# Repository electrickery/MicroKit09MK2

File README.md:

## Description

In several 1983 editions of the French computer magazine 'Led' an MC6809 
single board computer was published, supporting a 6-digit, 7-segment Led 
display and 34 keys. The original has a 2 kByte monitor ROM and 2 kByte 
RAM. 

<p align="center">

Most published material can be found here: 
https://lab.nethence.com/frederic/Microit09/

This is a recreation, with a smaller footprint and some room for 
expansion.

The original, published monitor version is 1.8. This repository contains
my minor enhancements.

My webpage on the subject can be found here: 
http://electrickery.nl/comp/microKit09/

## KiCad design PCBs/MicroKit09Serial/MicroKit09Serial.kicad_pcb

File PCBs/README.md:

MicroKit09 and MicroKit09_OI are the CPU and I/O (display, keyboard & 
cassette interface) boards.

The main differences from the 1980's original are:
* the form factor, 
* inter-board connector, 
* display type,
* keyboard construction,
* expansion connector (most pins use the 6809 pinout),
* ROM-size jumper (2 kByte / 4 kByte),
* RAM size jumper (2 kByte / 8 kByte),
* controllable LED on CPU-board (connects to PIA-CB2, also cassette out),
* added more address decoding for the I/O segment at A000h, reducing the
  memory range of the PIA to 1 kByte (was 8 kByte). A chip-select signal
  for A400h-A7FFh is available on the expansion connector.

MicroKit09Serial is the (as yet) untested serial interface.

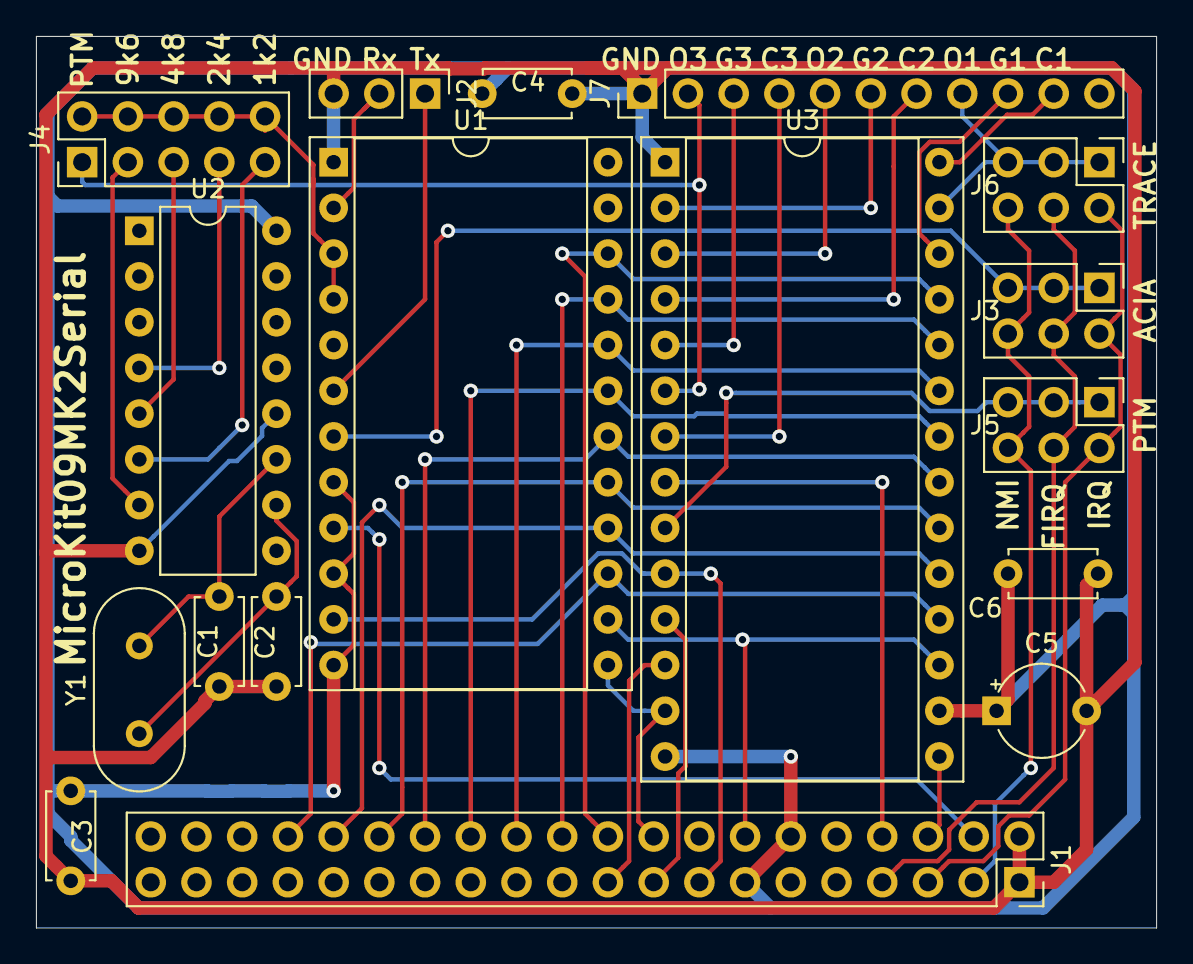
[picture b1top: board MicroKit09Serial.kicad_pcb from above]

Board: 2 copper layers, 62.2 x 49.5 mm, 17 parts (0 on the bottom side), 41 nets.

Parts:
C1, C2: 22pF; C_Disc_D4.7mm_W2.5mm_P5.00mm
C3, C4, C6: 100nF; C_Disc_D4.7mm_W2.5mm_P5.00mm
C5: 100uF/16V; CP_Radial_Tantal_D5.0mm_P5.00mm
J1: ExpansionConnector; PinHeader_2x20_P2.54mm_Vertical_CW
J2: Serial; PinHeader_1x03_P2.54mm_Vertical
J3: ACIA_INT; PinHeader_2x03_P2.54mm_Vertical
J4: BaudrateSelect; PinHeader_2x05_P2.54mm_Vertical
J5: PTM_INT; PinHeader_2x03_P2.54mm_Vertical
J6: TRACE_INT; PinHeader_2x03_P2.54mm_Vertical
J7: PTM; PinHeader_1x11_P2.54mm_Vertical
U1: MC6850; DIP-24_W15.24mm_Socket
U2: 4060N; DIP-16_W7.62mm
U3: MC6840; DIP-28_W15.24mm_Socket
Y1: 2.4576MHz; Crystal_HC49-U_Vertical

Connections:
+5V: C3.1, C4.1, C5.1, C6.1, J1.7, J1.35, U1.8, U1.10, U1.12, U2.16, U3.14, U3.16
/1200Bd: J4.9, U2.6
/2400Bd: J4.7, U2.4
/4800Bd: J4.5, U2.5
/9600Bd: J4.3, U2.7
/A0: J1.8, U1.11, U3.10
/A1: J1.9, U3.11
/A2: J1.10, U3.12
/A400-A7FF*: J1.39, U1.9
/A800-ABFF*: J1.38, U3.15
/ACIA_IRQ*: J3.1, J3.3, J3.5, U1.7
/BaudRate: J4.2, J4.4, J4.6, J4.8, J4.10, U1.3, U1.4
/D0: J1.31, U1.22, U3.25
/D1: J1.30, U1.21, U3.24
/D2: J1.29, U1.20, U3.23
/D3: J1.28, U1.19, U3.22
/D4: J1.27, U1.18, U3.21
/D5: J1.26, U1.17, U3.20
/D6: J1.25, U1.16, U3.19
/D7: J1.24, U1.15, U3.18
/E: J1.34, U1.14, U3.17
/FIRQ*: J1.4, J3.4, J5.4, J6.4
/IRQ*: J1.3, J3.2, J5.2, J6.2
/NMI*: J1.2, J3.6, J5.6, J6.6
/PTM_C1*: J7.10, U3.28
/PTM_C2*: J7.7, U3.4
/PTM_C3*: J7.4, U3.7
/PTM_G1*: J7.9, U3.26
/PTM_G2*: J7.6, U3.2
/PTM_G3*: J7.3, U3.5
/PTM_IRQ*: J5.1, J5.3, J5.5, U3.9
/PTM_O1: J6.1, J6.3, J6.5, J7.8, U3.27
/PTM_O2: J7.5, U3.3
/PTM_O3: J4.1, J7.2, U3.6
/RESET*: J1.37, U3.8
/RW*: J1.32, U1.13, U3.13
GND: C1.2, C2.2, C3.2, C4.2, C5.2, C6.2, J1.1, J1.40, J2.3, J7.1, U1.1, U2.8, U2.12, U3.1
unnamed: C1.1, U2.11, Y1.2
unnamed: C2.1, U2.10, Y1.1
unnamed: J2.1, U1.6
unnamed: J2.2, U1.2

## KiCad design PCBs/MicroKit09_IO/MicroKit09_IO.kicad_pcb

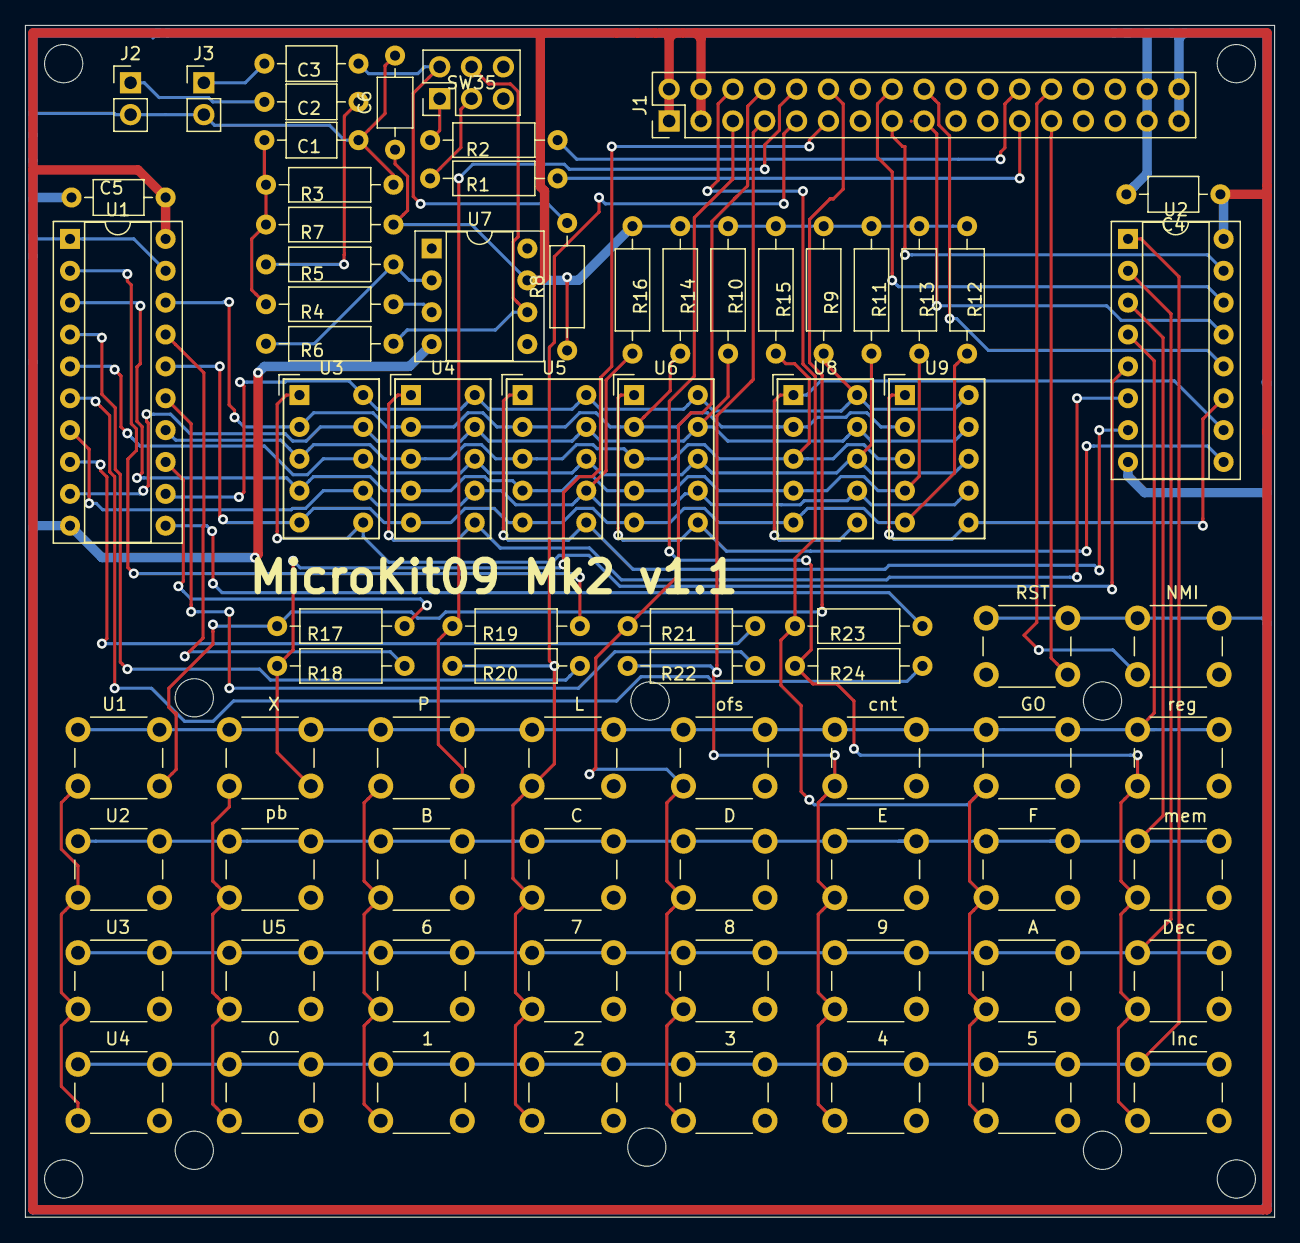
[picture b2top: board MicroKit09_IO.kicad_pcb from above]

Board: 2 copper layers, 99.6 x 95.0 mm, 77 parts (0 on the bottom side), 54 nets.

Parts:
C1, C2, C3, C4, C5: 100nF; C_Axial_L3.8mm_D2.6mm_P7.50mm_Horizontal
C6: 10uF; C_Axial_L3.8mm_D2.6mm_P7.50mm_Horizontal
J1: I/O-connector; PinHeader_2x17_P2.54mm_Vertical
J2: input; PinHeader_1x02_P2.54mm_Vertical
J3: output; PinHeader_1x02_P2.54mm_Vertical
R1, R2: 4k7; R_Axial_DIN0207_L6.3mm_D2.5mm_P10.16mm_Horizontal
R3: 27k; R_Axial_DIN0207_L6.3mm_D2.5mm_P10.16mm_Horizontal
R4, R5, R7: 10k; R_Axial_DIN0207_L6.3mm_D2.5mm_P10.16mm_Horizontal
R6: 1M; R_Axial_DIN0207_L6.3mm_D2.5mm_P10.16mm_Horizontal
R8: 470; R_Axial_DIN0207_L6.3mm_D2.5mm_P10.16mm_Horizontal
R9, R10, R11, R12, R13, R14, R15, R16: 120; R_Axial_DIN0207_L6.3mm_D2.5mm_P10.16mm_Horizontal
R17, R18, R19, R20, R21, R22, R23, R24: 5k6; R_Axial_DIN0207_L6.3mm_D2.5mm_P10.16mm_Horizontal
SW1: U1; SW_PUSH_6mm_H5mm
SW2: U2; SW_PUSH_6mm_H5mm
SW3: U3; SW_PUSH_6mm_H5mm
SW4: U4; SW_PUSH_6mm_H5mm
SW5: X; SW_PUSH_6mm_H5mm
SW6: pb; SW_PUSH_6mm_H5mm
SW7: U5; SW_PUSH_6mm_H5mm
SW8: 0; SW_PUSH_6mm_H5mm
SW9: P; SW_PUSH_6mm_H5mm
SW10: B; SW_PUSH_6mm_H5mm
SW11: 6; SW_PUSH_6mm_H5mm
SW12: 1; SW_PUSH_6mm_H5mm
SW13: L; SW_PUSH_6mm_H5mm
SW14: C; SW_PUSH_6mm_H5mm
SW15: 7; SW_PUSH_6mm_H5mm
SW16: 2; SW_PUSH_6mm_H5mm
SW17: ofs; SW_PUSH_6mm_H5mm
SW18: D; SW_PUSH_6mm_H5mm
SW19: 8; SW_PUSH_6mm_H5mm
SW20: 3; SW_PUSH_6mm_H5mm
SW21: cnt; SW_PUSH_6mm_H5mm
SW22: E; SW_PUSH_6mm_H5mm
SW23: 9; SW_PUSH_6mm_H5mm
SW24: 4; SW_PUSH_6mm_H5mm
SW25: GO; SW_PUSH_6mm_H5mm
SW26: F; SW_PUSH_6mm_H5mm
SW27: A; SW_PUSH_6mm_H5mm
SW28: 5; SW_PUSH_6mm_H5mm
SW29: reg; SW_PUSH_6mm_H5mm
SW30: mem; SW_PUSH_6mm_H5mm
SW31: Dec; SW_PUSH_6mm_H5mm
SW32: Inc; SW_PUSH_6mm_H5mm
SW33: NMI; SW_PUSH_6mm_H5mm
SW34: RST; SW_PUSH_6mm_H5mm
SW35: Cassette; PinHeader_2x03_P2.54mm_Vertical
U1: 74LS240; DIP-20_W7.62mm_Socket
U2: 74LS42; DIP-16_W7.62mm_Socket
U3, U4, U5, U6, U8, U9: HDSP-A153; HDSP-A151
U7: CA3140; DIP-8_W7.62mm_Socket

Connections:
+5V: C4.1, C5.1, C6.1, J1.1, J1.2, J1.3, J1.4, R3.2, R8.1, R9.2, R10.2, R11.2, R12.2, R13.2, R14.2, R15.2, R16.2, U1.20, U2.16, U7.7
/CB1: J1.23, R1.1
/CB2: J1.24, R2.1
/NMI*: J1.26, SW33.2
/PA0: J1.5, R24.2, SW29.2, SW30.2, SW31.2, SW32.2
/PA1: J1.6, R23.2, SW25.2, SW26.2, SW27.2, SW28.2
/PA2: J1.7, R22.2, SW21.2, SW22.2, SW23.2, SW24.2
/PA3: J1.8, R21.2, SW17.2, SW18.2, SW19.2, SW20.2
/PA4: J1.9, R20.2, SW13.2, SW14.2, SW15.2, SW16.2
/PA5: J1.10, R19.2, SW9.2, SW10.2, SW11.2, SW12.2
/PA6: J1.11, R18.2, SW5.2, SW6.2, SW7.2, SW8.2
/PA7: J1.12, R17.2, SW1.2, SW2.2, SW3.2, SW4.2
/PB0: J1.15, U2.15
/PB1: J1.16, U2.14
/PB2: J1.17, U2.13
/PB3: J1.18, U2.12
/R1: SW4.1, SW8.1, SW12.1, SW16.1, SW20.1, SW24.1, SW28.1, SW32.1, U2.1
/R2: SW3.1, SW7.1, SW11.1, SW15.1, SW19.1, SW23.1, SW27.1, SW31.1, U2.2
/R3: SW2.1, SW6.1, SW10.1, SW14.1, SW18.1, SW22.1, SW26.1, SW30.1, U2.3
/R4: SW1.1, SW5.1, SW9.1, SW13.1, SW17.1, SW21.1, SW25.1, SW29.1, U2.4
/RESET*: J1.25, SW34.2
GND: C1.2, C4.2, C5.2, C6.2, J1.31, J1.32, J1.33, J1.34, J2.2, J3.2, R7.1, SW33.1, SW34.1, U1.1, U1.10, U1.19, U2.8, U7.4
unnamed: C1.1, R3.1, R4.1, R7.2
unnamed: C2.1, J2.1
unnamed: C2.2, R5.1
unnamed: C3.1, J3.1
unnamed: C3.2, R8.2, SW35.2
unnamed: R1.2, SW35.3
unnamed: R2.2, SW35.1
unnamed: R4.2, U7.3
unnamed: R5.2, R6.1, U7.2
unnamed: R6.2, SW35.4, U7.6
unnamed: R9.1, U1.12, U3.10, U4.10, U5.10, U6.10, U8.10, U9.10
unnamed: R10.1, U1.9, U3.9, U4.9, U5.9, U6.9, U8.9, U9.9
unnamed: R11.1, U1.5, U3.8, U4.8, U5.8, U6.8, U8.8, U9.8
unnamed: R12.1, U1.16, U3.5, U4.5, U5.5, U6.5, U8.5, U9.5
unnamed: R13.1, U1.3, U3.4, U4.4, U5.4, U6.4, U8.4, U9.4
unnamed: R14.1, U1.18, U3.2, U4.2, U5.2, U6.2, U8.2, U9.2
unnamed: R15.1, U1.14, U3.3, U4.3, U5.3, U6.3, U8.3, U9.3
unnamed: R16.1, U1.7, U3.7, U4.7, U5.7, U6.7, U8.7, U9.7
unnamed: R17.1, U1.13
unnamed: R18.1, U1.17
unnamed: R19.1, U1.2
unnamed: R20.1, U1.4
unnamed: R21.1, U1.8
unnamed: R22.1, U1.15
unnamed: R23.1, U1.11
unnamed: R24.1, U1.6
unnamed: U2.5, U3.1, U3.6
unnamed: U2.6, U4.1, U4.6
unnamed: U2.7, U5.1, U5.6
unnamed: U2.9, U6.1, U6.6
unnamed: U2.10, U8.1, U8.6
unnamed: U2.11, U9.1, U9.6

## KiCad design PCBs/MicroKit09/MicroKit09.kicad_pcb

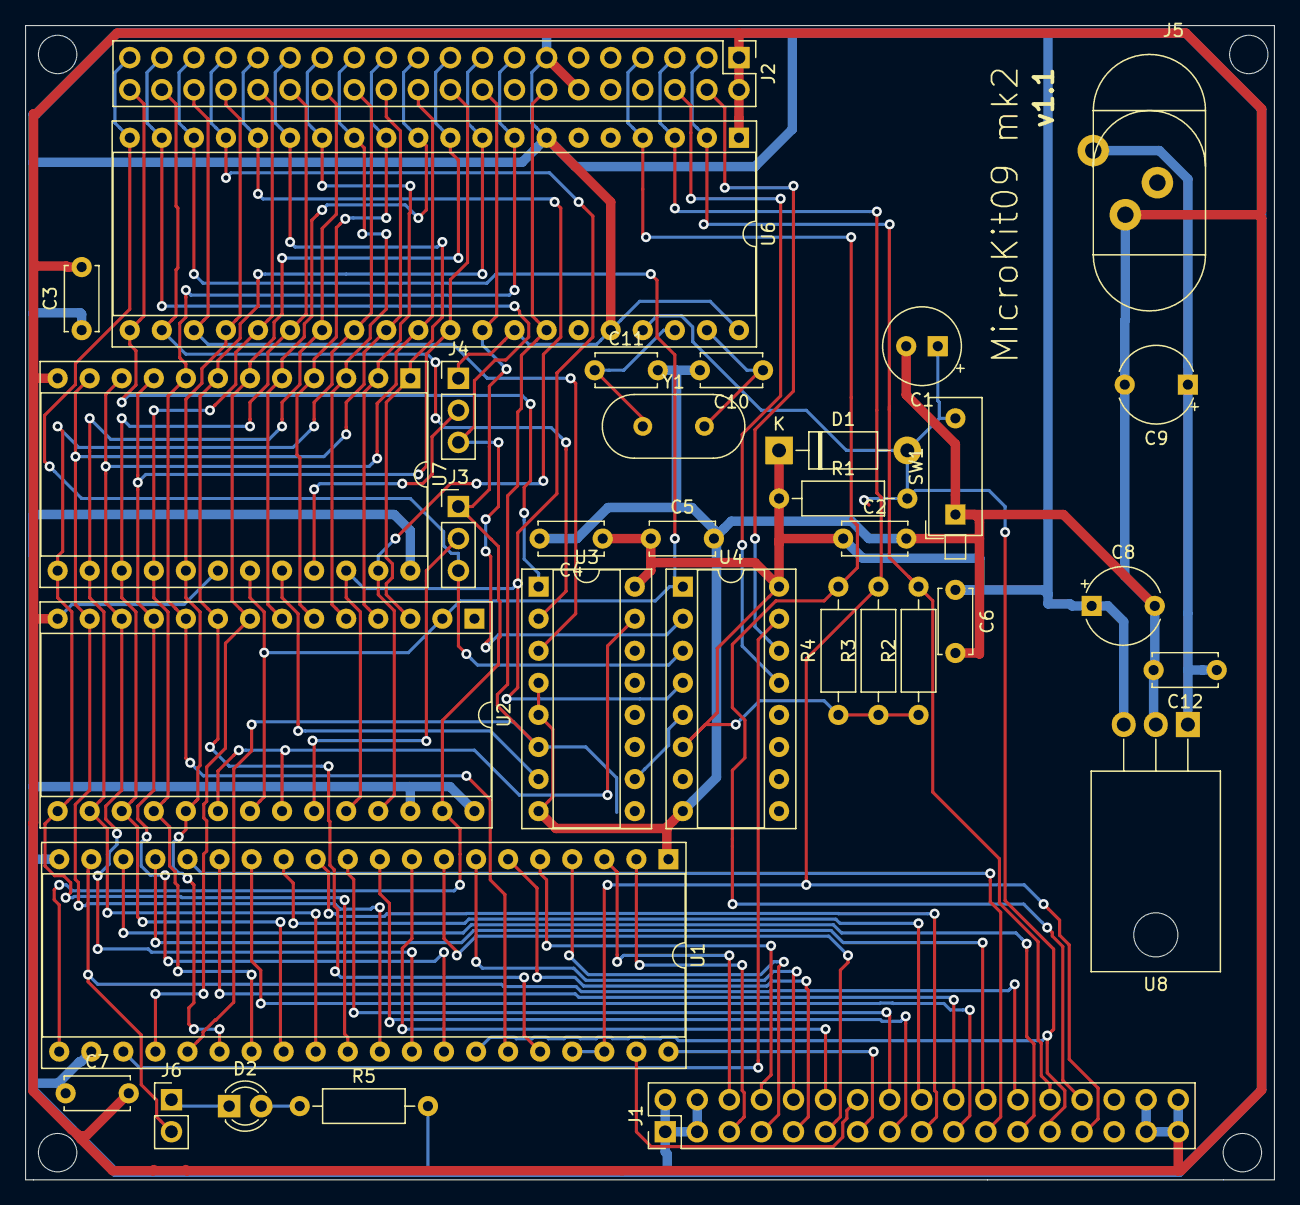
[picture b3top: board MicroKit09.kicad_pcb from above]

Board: 2 copper layers, 98.9 x 91.4 mm, 34 parts (0 on the bottom side), 65 nets.

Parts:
C1: 22uF; CP_Radial_Tantal_D6.0mm_P2.50mm
C2, C3, C4, C5, C6, C7, C12: 100nF; C_Disc_D5.0mm_W2.5mm_P5.00mm
C8: 10uF/16V; CP_Radial_Tantal_D6.0mm_P5.00mm
C9: 100uF/25V; CP_Radial_Tantal_D6.0mm_P5.00mm
C10, C11: 22pF; C_Disc_D4.7mm_W2.5mm_P5.00mm
D1: D_Schottky_Small; D_DO-41_SOD81_P10.16mm_Horizontal
D2: Green; LED_D3.0mm
J1: I/O-board; PinHeader_2x17_P2.54mm_Vertical
J2: ExtensionConnector; PinHeader_2x20_P2.54mm_Vertical_CC
J3: 2k/8k; PinHeader_1x03_P2.54mm_Vertical
J4: 2k/4k; PinHeader_1x03_P2.54mm_Vertical
J5: Power; Barrel_Jack_vertical_alt
J6: LED enable; PinHeader_1x02_P2.54mm_Vertical
R1: 5k6; R_Axial_DIN0207_L6.3mm_D2.5mm_P10.16mm_Horizontal
R2, R3, R4: 3k3; R_Axial_DIN0207_L6.3mm_D2.5mm_P10.16mm_Horizontal
R5: 330; R_Axial_DIN0207_L6.3mm_D2.5mm_P10.16mm_Horizontal
SW1: Reset; SW_DIP_SPSTx01_Piano_10.8x4.1mm_W7.62mm_P2.54mm
U1: 6821; DIP-40_W15.24mm_Socket
U2: 6264_alt; DIP-28_W15.24mm_Socket
U3, U4: 74LS138; DIP-16_W7.62mm_Socket
U6: MC6809; DIP-40_W15.24mm_Socket
U7: 2732_alt; DIP-24_W15.24mm_Socket
U8: LM7805_TO220; TO-220-3_Horizontal_TabDown
Y1: 4MHz; Crystal_HC49-U_Vertical

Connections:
+5V: C2.1, C3.1, C4.1, C5.1, C6.1, C7.1, C8.1, D1.1, J1.1, J1.2, J1.3, J1.4, J2.7, J2.35, J4.1, R1.1, R2.1, R3.1, R4.1, R5.2, U1.20, U1.22, U2.26, U2.28, U3.16, U4.6, U4.16, U6.7, U6.33, U6.36, U6.40, U7.24, U8.3
/A0: J2.8, U1.35, U2.10, U6.8, U7.8
/A000-A3FF: U1.23, U4.15
/A1: J2.9, U1.36, U2.9, U6.9, U7.7
/A2: J2.10, U1.24, U2.8, U6.10, U7.6
/A3: J2.11, U2.7, U6.11, U7.5
/A4: J2.12, U2.6, U6.12, U7.4
/A5: J2.13, U2.5, U6.13, U7.3
/A6: J2.14, U2.4, U6.14, U7.2
/A7: J2.15, U2.3, U6.15, U7.1
/A8: J2.16, U2.25, U6.16, U7.23
/A9: J2.17, U2.24, U4.4, U6.17, U7.22
/A10: J2.18, U2.2, U2.21, U4.1, U6.18, U7.19
/A11: J2.19, J4.3, U4.2, U6.19
/A11_Vpp: J4.2, U7.21
/A11_WR*: J3.2, U2.23
/A12: J2.20, J3.3, U4.3, U6.20
/A13: J2.21, U3.1, U6.21
/A14: J2.22, U3.2, U6.22
/A15: J2.23, U3.3, U6.23
/A400-A7FF*: J2.39, U4.14
/A800-ABFF*: J2.38, U4.13
/CA1: J1.13, U1.40
/CA2: J1.14, U1.39
/CB1: J1.23, U1.18
/CB2: J1.24, J6.2, U1.19
/D0: J2.31, U1.33, U2.11, U6.31, U7.9
/D1: J2.30, U1.32, U2.12, U6.30, U7.10
/D2: J2.29, U1.31, U2.13, U6.29, U7.11
/D3: J2.28, U1.30, U2.15, U6.28, U7.13
/D4: J2.27, U1.29, U2.16, U6.27, U7.14
/D5: J2.26, U1.28, U2.17, U6.26, U7.15
/D6: J2.25, U1.27, U2.18, U6.25, U7.16
/D7: J2.24, U1.26, U2.19, U6.24, U7.17
/E: J2.34, U1.25, U3.6, U6.34
/FIRQ*: J1.28, J2.4, R4.2, U6.4
/IRQ*: J1.27, J2.3, R3.2, U1.37, U1.38, U6.3
/NMI*: J1.26, J2.2, R2.2, U6.2
/PA0: J1.5, U1.2
/PA1: J1.6, U1.3
/PA2: J1.7, U1.4
/PA3: J1.8, U1.5
/PA4: J1.9, U1.6
/PA5: J1.10, U1.7
/PA6: J1.11, U1.8
/PA7: J1.12, U1.9
/PB0: J1.15, U1.10
/PB1: J1.16, U1.11
/PB2: J1.17, U1.12
/PB3: J1.18, U1.13
/PB4: J1.19, U1.14
/PB5: J1.20, U1.15
/PB6: J1.21, U1.16
/PB7: J1.22, U1.17
/RESET*: C1.1, D1.2, J1.25, R1.2, SW1.2, U1.34, U6.37
/RW*: J2.32, J3.1, U1.21, U2.27, U6.32
GND: C1.2, C2.2, C3.2, C4.2, C5.2, C6.2, C7.2, C8.2, C9.2, C10.2, C11.2, C12.2, J1.31, J1.32, J1.33, J1.34, J2.1, J2.40, J5.2, SW1.1, U1.1, U2.14, U3.4, U3.5, U3.8, U4.8, U6.1, U7.12, U7.18, U8.2
unnamed: C10.1, U6.39, Y1.2
unnamed: C11.1, U6.38, Y1.1
unnamed: C9.1, C12.1, J5.1, U8.1
unnamed: D2.1, J6.1
unnamed: D2.2, R5.1
unnamed: U2.20, U2.22, U3.15
unnamed: U3.7, U7.20
unnamed: U3.10, U4.5

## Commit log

2021-04-15 Initial monitor version and corrected PCBs and 3D-printed parts.
2021-04-15 Updated the monitor to version 1.9.
2021-04-15 Documentation updates.
2021-04-15 Documentation update.
2021-04-15 Documentation update 2.
2021-04-15 Documentation update 3.
2021-04-27 Added low-profile keyboard parts.
2021-04-27 Reverted ORG location to E000h.
2021-12-26 Updated web site address and fixed minor typo.
2024-08-12 First working version of the serial monitor.
2024-08-12 Changed to 4 kByte ROM, added the '6809uP' demo.
2024-08-14 Rudimentary 16 byte data dump.
2025-07-19 Assembler format switch, minor additions. Almost working "memory-present" indicator.
2025-07-29 Added 6309 check to banner, fixed key test routine.
2025-07-29 Insterted the processor check/banner at startup.
2025-09-03 ASSIST09 source code added compatible with the MicroKit09MK2 serial/timer extension.
2025-09-04 Correct version of the ASSIST09 monitor source and some documentation.
2025-09-04 Markdown typo fix.
